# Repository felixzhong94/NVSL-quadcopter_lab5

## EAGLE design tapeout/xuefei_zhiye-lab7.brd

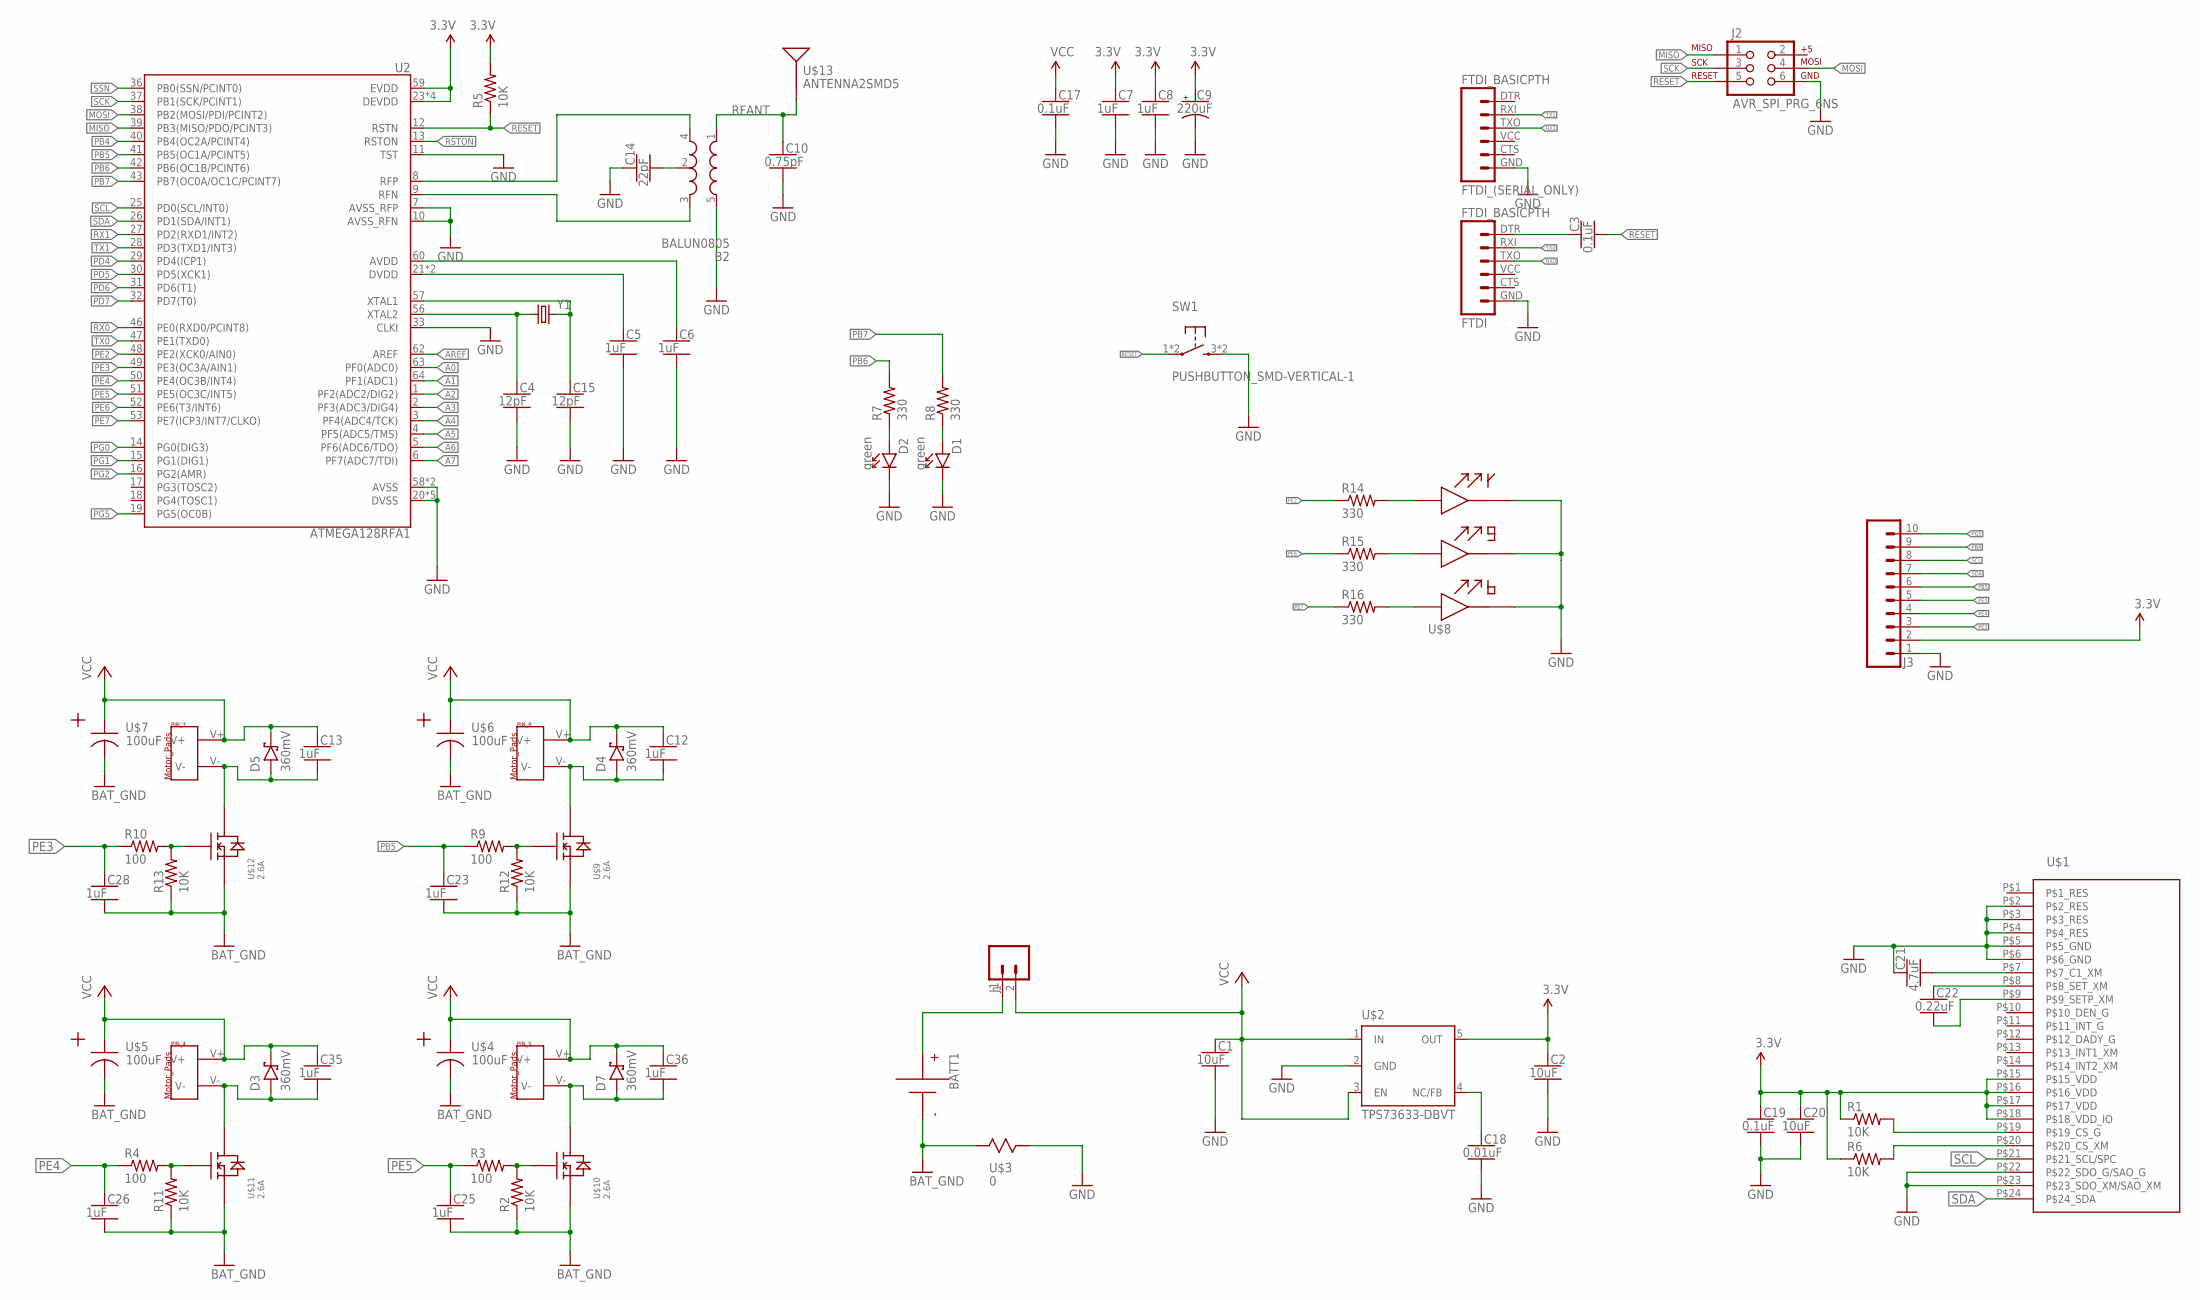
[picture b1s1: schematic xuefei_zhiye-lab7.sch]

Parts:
B2: BALUN0805; BALUN
BATT1: BATTERY-HUBSAN-W/HOLDER; BATTERY-W/HOLDER-380MAH-HUBSAN
C1, C2, C20: 10uF; CAPC2012X140_HS
C3, C17, C19: 0.1uF; CAPC2012X140_HS
C4, C15: 12pF; CAPC2012X140_HS
C5, C6, C7, C8, C12, C13, C23, C25, C26, C28, C35, C36: 1uF; CAPC2012X140_HS
C9: 220uF; CAPMP7343X310_HS
C10: 0.75pF; CAPC2012X140_HS
C14: 22pF; CAPC2012X140_HS
C18: 0.01uF; CAPC2012X140_HS
C21: 4.7uF; CAPC2012X140_HS
C22: 0.22uF; CAPC2012X140_HS
D1, D2: green; LEDSC125X200X120-2_HS
D3, D4, D5, D7: 360mV; SOD3716X135_HS
FTDI: FTDI_BASICPTH; FTDI_BASIC
FTDI_(SERIAL_ONLY): FTDI_BASICPTH; FTDI_BASIC
J1: MALE_HEADER_2POS-2X1-0.1IN; MALE_HEADER_2X1_0.1IN
J2: AVR_SPI_PRG_6NS; 2X3-NS
J3: SIP-10_TH-254X10-1; HDRV10W63P254_10X1_2540X254H838_HS
PIN_3, PIN_4, PIN_5, PIN_8: MOTOR_PADS
R1, R2, R5, R6, R11, R12, R13: 10K; RESC2012X60_HS
R3, R4, R9, R10: 100; RESC2012X60_HS
R7, R8, R14, R15, R16: 330; RESC2012X60_HS
SW1: PUSHBUTTON_SMD-VERTICAL-1; TE_FSM8JSMA_HS
U2: ATMEGA128RFA1; QFN-64
U$1: IMU; LGA-24_4X4MM
U$2: TPS73633-DBVT; SOT23-DBV
U$3: 0; SMD_RESISTOR
U$4, U$5, U$6, U$7: 100uF; TAJB_SMB_POLAR_CAP
U$8: QBLP679E-RGB
U$9, U$10, U$11, U$12: 2.6A; LITTLE_FOOT_MOSFET_W/_HEAT_SPREADER
U$13: ANTENNA2SMD5; ANTENNA-CHIP5
Y1: CRYSTAL5X3; CRYSTAL-SMD-5X3

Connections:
3.3V: C2.1, C7.1, C8.1, C9.1 (+), C19.1, C20.1, J3.2, R1.1, R5.2, R6.1, U2.23 (DEVDD), U2.34 (DEVDD), U2.44 (DEVDD), U2.54 (DEVDD), U2.59 (EVDD), U$1.P$15 (P$15_VDD), U$1.P$16 (P$16_VDD), U$1.P$17 (P$17_VDD), U$1.P$18 (P$18_VDD_IO), U$2.5 (OUT)
A0: U2.63 (PF0(ADC0))
A1: U2.64 (PF1(ADC1))
A2: U2.1 (PF2(ADC2/DIG2))
A3: U2.2 (PF3(ADC3/DIG4))
A4: U2.3 (PF4(ADC4/TCK))
A5: U2.4 (PF5(ADC5/TMS))
A6: U2.5 (PF6(ADC6/TDO))
A7: U2.6 (PF7(ADC7/TDI))
AREF: U2.62 (AREF)
AVDD: C6.1, U2.60 (AVDD)
BAT_GND: BATT1.- (N), C23.2, C25.2, C26.2, C28.2, R2.1, R11.1, R12.1, R13.1, U$3.P$1, U$4.P$2 (2), U$5.P$2 (2), U$6.P$2 (2), U$7.P$2 (2), U$9.P$2 (P$2_S), U$10.P$2 (P$2_S), U$11.P$2 (P$2_S), U$12.P$2 (P$2_S)
DTR: C3.1, FTDI.DTR (1)
DVDD: C5.1, U2.21 (DVDD), U2.22 (DVDD)
GND: B2.5 (GND), C1.2, C2.2, C4.2, C5.2, C6.2, C7.2, C8.2, C9.2 (-), C10.2, C14.1, C15.2, C17.2, C18.2, C19.2, C20.2, C21.1, D1.C, D2.C, FTDI.GND (6), FTDI_(SERIAL_ONLY).GND (6), J2.6, J3.1, SW1.3 (2), SW1.4 (2), U2.7 (AVSS_RFP), U2.10 (AVSS_RFN), U2.11 (TST), U2.20 (DVSS), U2.24 (DVSS), U2.33 (CLKI), U2.35 (DVSS), U2.45 (DVSS), U2.55 (DVSS), U2.58 (AVSS), U2.61 (AVSS), U$1.P$2 (P$2_RES), U$1.P$3 (P$3_RES), U$1.P$4 (P$4_RES), U$1.P$5 (P$5_GND), U$1.P$6 (P$6_GND), U$1.P$22 (P$22_SDO_G/SAO_G), U$1.P$23 (P$23_SDO_XM/SAO_XM), U$2.2 (GND), U$3.P$2, U$8.P$1, U$8.P$2, U$8.P$3
MISO: J2.1, U2.39 (PB3(MISO/PDO/PCINT3))
MOSI: J2.4, U2.38 (PB2(MOSI/PDI/PCINT2))
unnamed: R14.2, U$8.P$4
unnamed: R15.2, U$8.P$5
unnamed: C15.1, U2.57 (XTAL1), Y1.3 (2)
unnamed: C4.1, U2.56 (XTAL2), Y1.1
unnamed: C18.1, U$2.4 (NC/FB)
unnamed: C21.2, U$1.P$7 (P$7_C1_XM)
unnamed: B2.2 (GND), C14.2
unnamed: D2.A, R7.1
unnamed: R16.2, U$8.P$6
unnamed: C22.1, U$1.P$8 (P$8_SET_XM)
unnamed: D1.A, R8.1
unnamed: C22.2, U$1.P$9 (P$9_SETP_XM)
unnamed: R1.2, U$1.P$19 (P$19_CS_G)
unnamed: R6.2, U$1.P$20 (P$20_CS_XM)
unnamed: BATT1.+, J1.1
unnamed: R9.2, R12.2, U$9.P$1 (P$1_G)
unnamed: C12.2, D4.A, PIN_8.V-, U$9.P$3 (P$3_D)
unnamed: R2.2, R3.2, U$10.P$1 (P$1_G)
unnamed: C36.2, D7.A, PIN_5.V-, U$10.P$3 (P$3_D)
unnamed: R10.2, R13.2, U$12.P$1 (P$1_G)
unnamed: C13.2, D5.A, PIN_3.V-, U$12.P$3 (P$3_D)
unnamed: R4.2, R11.2, U$11.P$1 (P$1_G)
unnamed: C35.2, D3.A, PIN_4.V-, U$11.P$3 (P$3_D)
PB4: J3.9, U2.40 (PB4(OC2A/PCINT4))
PB5: C23.1, J3.6, R9.1, U2.41 (PB5(OC1A/PCINT5))
PB6: R7.2, U2.42 (PB6(OC1B/PCINT6))
PB7: R8.2, U2.43 (PB7(OC0A/OC1C/PCINT7))
PD4: U2.29 (PD4(ICP1))
PD5: U2.30 (PD5(XCK1))
PD6: U2.31 (PD6(T1))
PD7: U2.32 (PD7(T0))
PE2: R14.1, U2.48 (PE2(XCK0/AIN0))
PE3: C28.1, J3.3, R10.1, U2.49 (PE3(OC3A/AIN1))
PE4: C26.1, J3.4, R4.1, U2.50 (PE4(OC3B/INT4))
PE5: C25.1, J3.5, R3.1, U2.51 (PE5(OC3C/INT5))
PE6: R15.1, U2.52 (PE6(T3/INT6))
PE7: R16.1, U2.53 (PE7(ICP3/INT7/CLKO))
PG0: U2.14 (PG0(DIG3))
PG1: U2.15 (PG1(DIG1))
PG2: U2.16 (PG2(AMR))
PG5: J3.10, U2.19 (PG5(OC0B))
RESET: C3.2, J2.5, R5.1, SW1.1, SW1.2 (1), U2.12 (RSTN)
RFANT: B2.1 (IN), C10.1, U$13.FEED
RFN: B2.3 (OUT2), U2.9 (RFN)
RFP: B2.4 (OUT1), U2.8 (RFP)
RSTON: U2.13 (RSTON)
RX0: FTDI.TXO (3), U2.46 (PE0(RXD0/PCINT8))
RX1: FTDI_(SERIAL_ONLY).TXO (3), U2.27 (PD2(RXD1/INT2))
SCK: J2.3, U2.37 (PB1(SCK/PCINT1))
SCL: J3.8, U2.25 (PD0(SCL/INT0)), U$1.P$21 (P$21_SCL/SPC)
SDA: J3.7, U2.26 (PD1(SDA/INT1)), U$1.P$24 (P$24_SDA)
SSN: U2.36 (PB0(SSN/PCINT0))
TX0: FTDI.RXI (2), U2.47 (PE1(TXD0))
TX1: FTDI_(SERIAL_ONLY).RXI (2), U2.28 (PD3(TXD1/INT3))
VCC: C1.1, C12.1, C13.1, C17.1, C35.1, C36.1, D3.C, D4.C, D5.C, D7.C, J1.2, PIN_3.V+, PIN_4.V+, PIN_5.V+, PIN_8.V+, U$2.1 (IN), U$2.3 (EN), U$4.P$1 (1), U$5.P$1 (1), U$6.P$1 (1), U$7.P$1 (1)

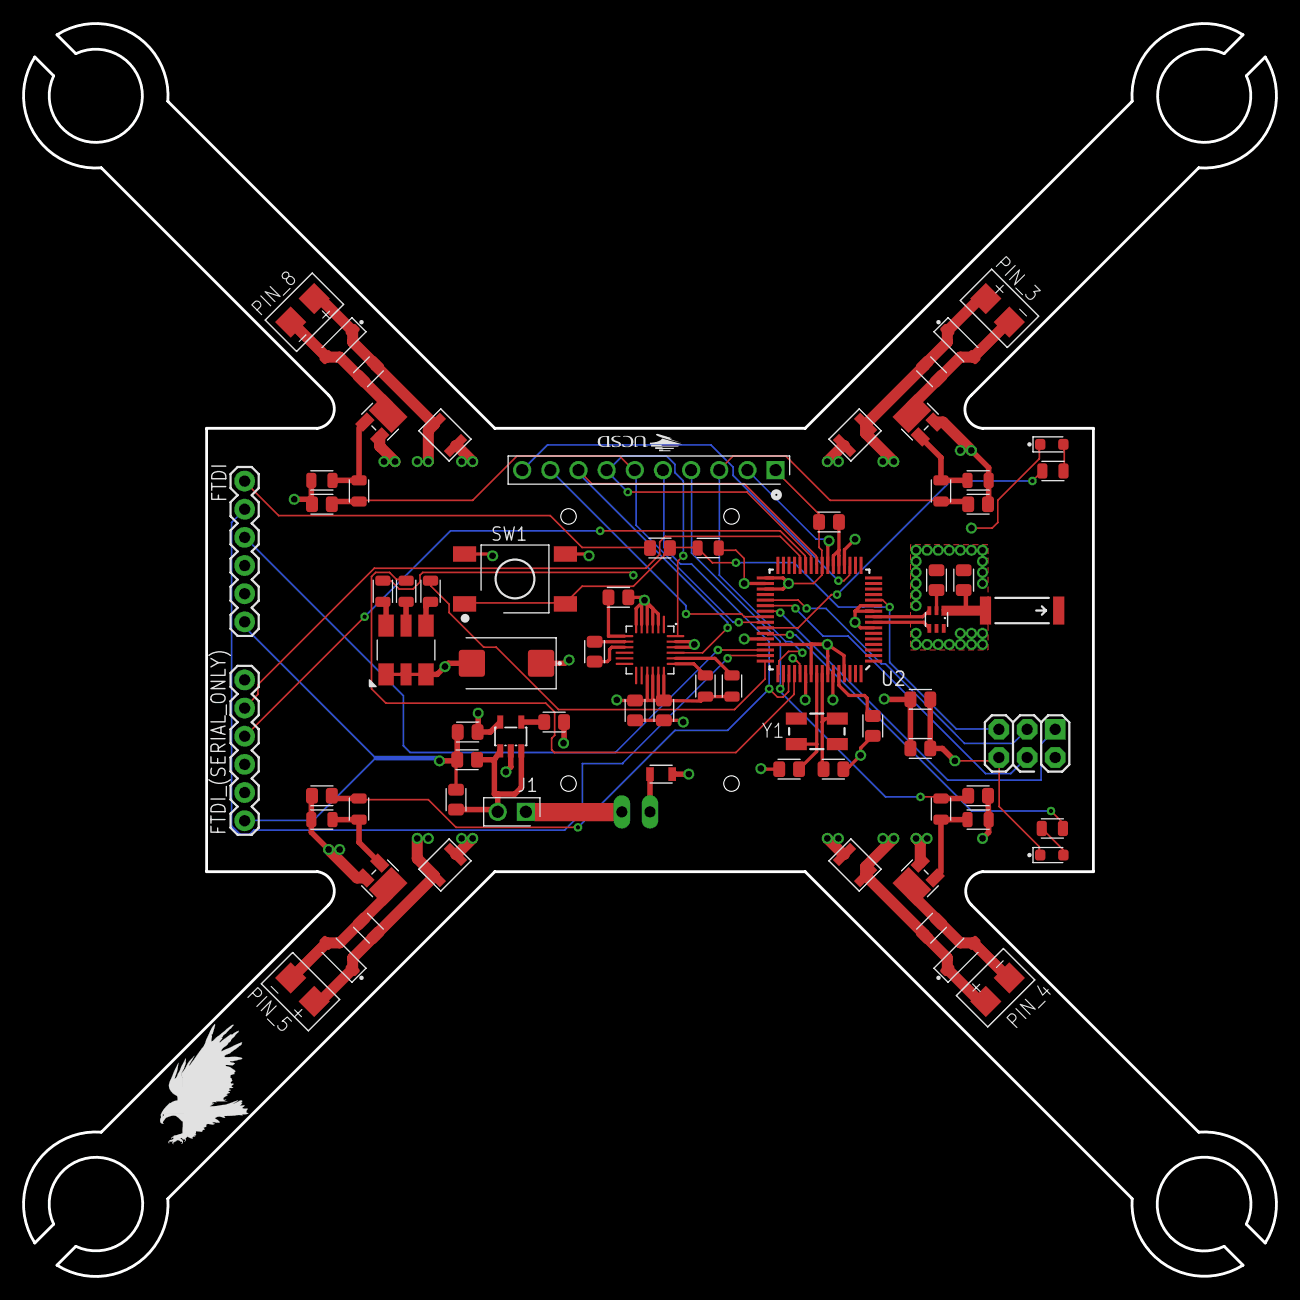
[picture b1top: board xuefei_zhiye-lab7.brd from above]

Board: 4 copper layers, 113.0 x 113.0 mm, 77 parts (1 on the bottom side), 54 nets.

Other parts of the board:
U$14: UCSD_LOGO
U$15: EAGLE-PLC-8MM

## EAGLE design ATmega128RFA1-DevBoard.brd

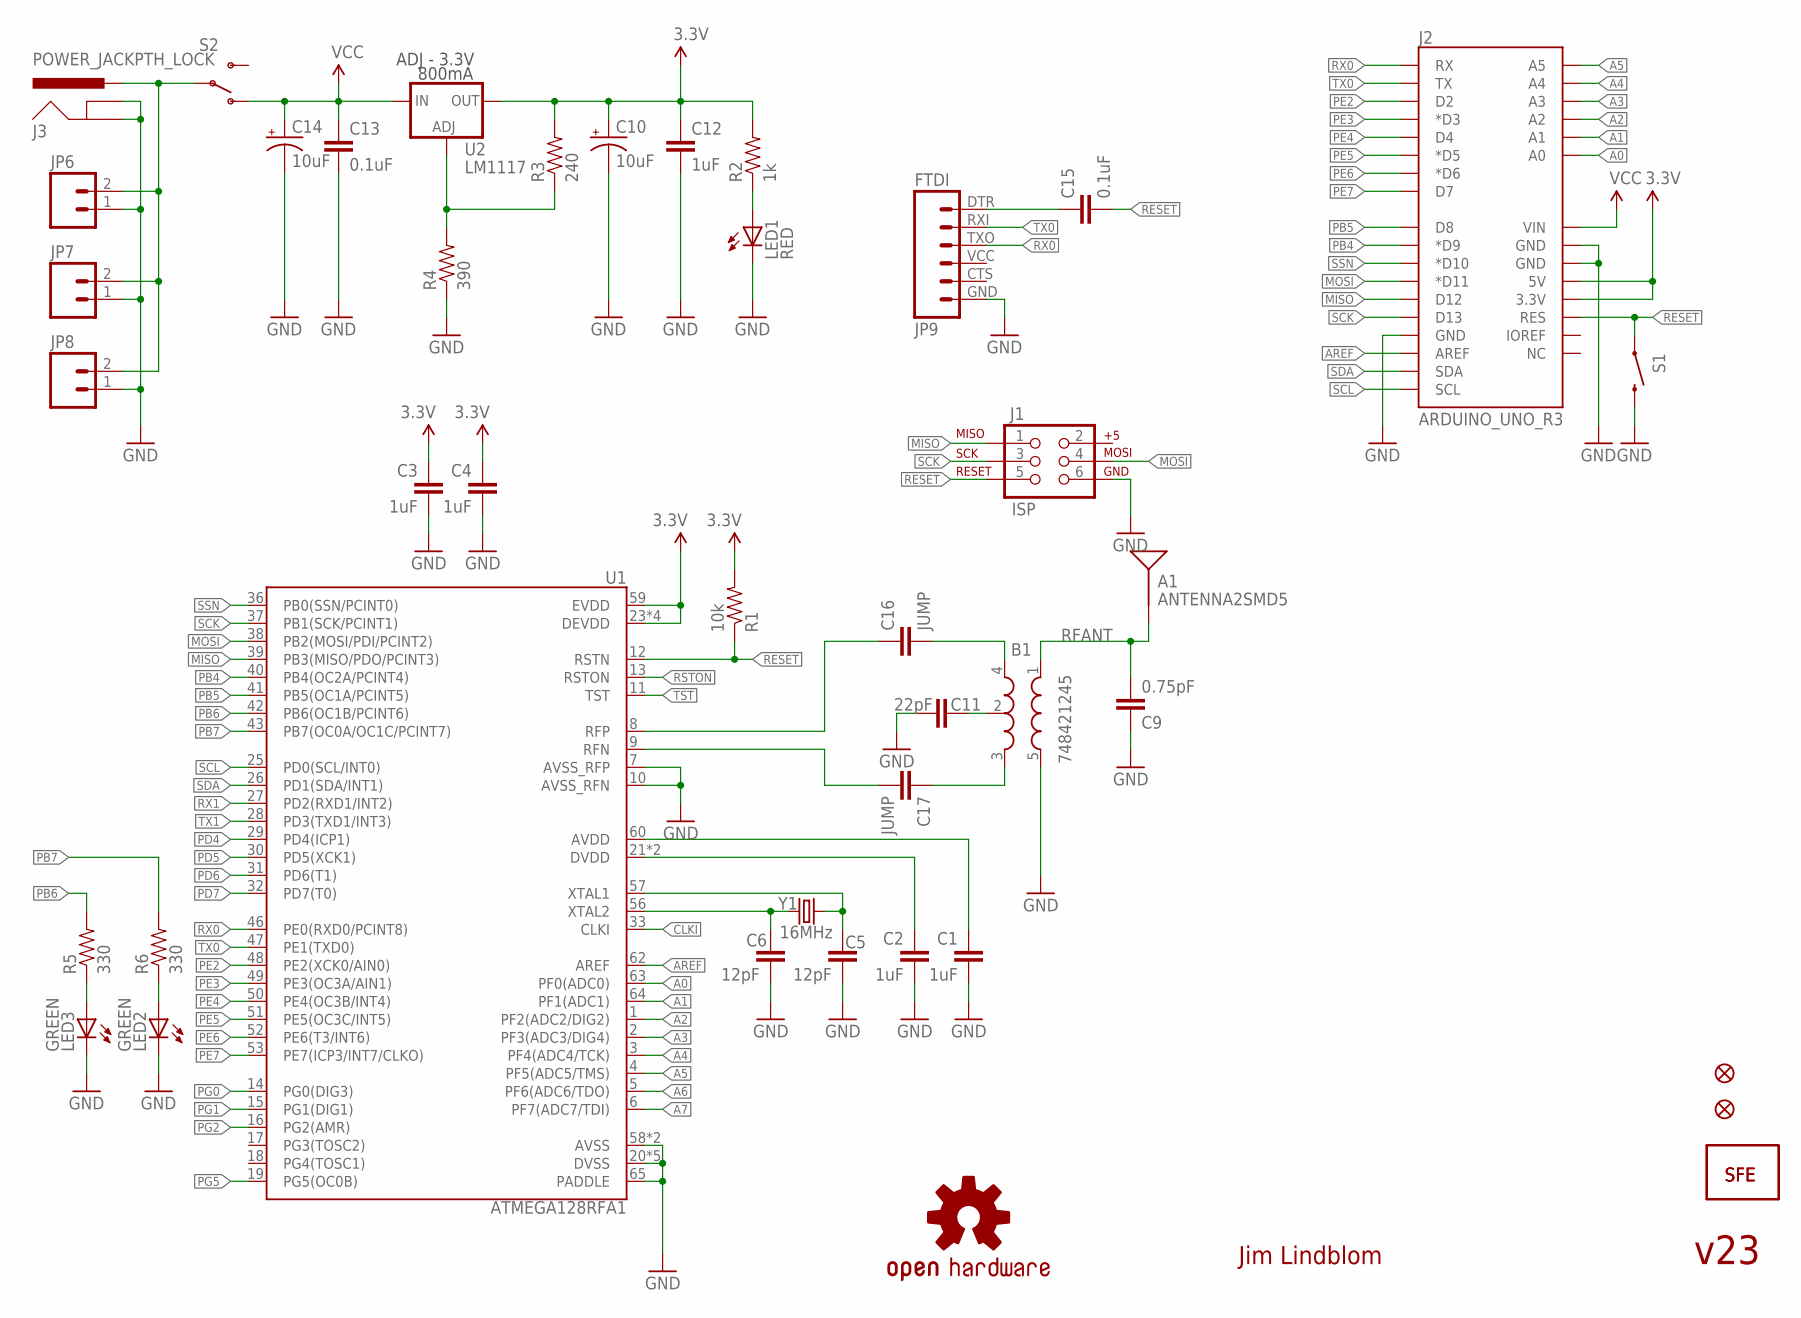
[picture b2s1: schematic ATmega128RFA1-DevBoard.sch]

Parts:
A1: ANTENNA2SMD5; ANTENNA-CHIP5
B1: 748421245; BALUN
C1, C2, C3, C4, C12: 1uF; 0402-CAP
C5, C6: 12pF; 0402-CAP
C9: 0.75pF; 0402-CAP
C10, C14: 10uF; EIA3216
C11: 22pF; 0402-CAP
C13, C15: 0.1uF; 0402-CAP
C16, C17: JUMP; 0402-CAP
FID1, FID2: FIDUCIALUFIDUCIAL; MICRO-FIDUCIAL
J1: ISP; 2X3-NS
J2: ARDUINO_UNO_R3
J3: POWER_JACKPTH_LOCK; POWER_JACK_PTH_LOCK
JP4, JP10: LOGO-SFENEW; SFE-NEW-WEBLOGO
JP6: M02JST-PTH-2; JST-2-PTH
JP7: M021X02_NO_SILK; 1X02_NO_SILK
JP8: M023.5MM-NO_SILK; SCREWTERMINAL-3.5MM-2-NS
JP9: FTDI; FTDI_BASIC
LED1: RED; LED-0603
LED2, LED3: GREEN; LED-0603
R1: 10k; 0402-RES
R2: 1k; 0402-RES
R3: 240; 0402-RES
R4: 390; 0402-RES
R5, R6: 330; 0402-RES
S1: SWITCH-MOMENTARY-2SMD; TACTILE_SWITCH_SMD
S2: SWITCH-SPST-SMD-A
U1: ATMEGA128RFA1; QFN-64
U2: LM1117; SOT223
U$1: OSHW-LOGOS; OSHW-LOGO-S
Y1: 16MHz; CRYSTAL-SMD-5X3

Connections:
3.3V: C3.1, C4.1, C10.A (+), C12.1, J2.3.3V, J2.5V, R1.2, R2.2, R3.2, U1.23 (DEVDD), U1.34 (DEVDD), U1.44 (DEVDD), U1.54 (DEVDD), U1.59 (EVDD), U2.2 (OUT)
A0: J2.A0, U1.63 (PF0(ADC0))
A1: J2.A1, U1.64 (PF1(ADC1))
A2: J2.A2, U1.1 (PF2(ADC2/DIG2))
A3: J2.A3, U1.2 (PF3(ADC3/DIG4))
A4: J2.A4, U1.3 (PF4(ADC4/TCK))
A5: J2.A5, U1.4 (PF5(ADC5/TMS))
A6: U1.5 (PF6(ADC6/TDO))
A7: U1.6 (PF7(ADC7/TDI))
AREF: J2.AREF, U1.62 (AREF)
AVDD: C1.1, U1.60 (AVDD)
CLKI: U1.33 (CLKI)
DTR: C15.1, JP9.DTR (1)
DVDD: C2.1, U1.21 (DVDD), U1.22 (DVDD)
FB: R3.1, R4.2, U2.1 (ADJ)
GND: B1.5 (GND), C1.2, C2.2, C3.2, C4.2, C5.2, C6.2, C9.1, C10.C (-), C11.2, C12.2, C13.2, C14.C (-), J1.6, J2.GND@0 (GND), J2.GND@1 (GND), J2.GND@2 (GND), J3.GND, J3.GNDBREAK, JP6.1, JP7.1, JP8.1, JP9.GND (6), LED1.C, LED2.C, LED3.C, R4.1, S1.3 (2), U1.7 (AVSS_RFP), U1.10 (AVSS_RFN), U1.20 (DVSS), U1.24 (DVSS), U1.35 (DVSS), U1.45 (DVSS), U1.55 (DVSS), U1.58 (AVSS), U1.61 (AVSS), U1.65 (PADDLE)
MISO: J1.1, J2.D12, U1.39 (PB3(MISO/PDO/PCINT3))
MOSI: J1.4, J2.D11 (*D11), U1.38 (PB2(MOSI/PDI/PCINT2))
unnamed: LED1.A, R2.1
unnamed: C5.1, U1.57 (XTAL1), Y1.3 (2)
unnamed: C6.1, U1.56 (XTAL2), Y1.1
unnamed: B1.2 (GND), C11.1
unnamed: LED3.A, R5.1
unnamed: J3.PWR, JP6.2, JP7.2, JP8.2, S2.2
unnamed: B1.4 (OUT1), C16.2
unnamed: B1.3 (OUT2), C17.1
unnamed: LED2.A, R6.1
PB4: J2.D9 (*D9), U1.40 (PB4(OC2A/PCINT4))
PB5: J2.D8, U1.41 (PB5(OC1A/PCINT5))
PB6: R5.2, U1.42 (PB6(OC1B/PCINT6))
PB7: R6.2, U1.43 (PB7(OC0A/OC1C/PCINT7))
PD4: U1.29 (PD4(ICP1))
PD5: U1.30 (PD5(XCK1))
PD6: U1.31 (PD6(T1))
PD7: U1.32 (PD7(T0))
PE2: J2.D2, U1.48 (PE2(XCK0/AIN0))
PE3: J2.D3 (*D3), U1.49 (PE3(OC3A/AIN1))
PE4: J2.D4, U1.50 (PE4(OC3B/INT4))
PE5: J2.D5 (*D5), U1.51 (PE5(OC3C/INT5))
PE6: J2.D6 (*D6), U1.52 (PE6(T3/INT6))
PE7: J2.D7, U1.53 (PE7(ICP3/INT7/CLKO))
PG0: U1.14 (PG0(DIG3))
PG1: U1.15 (PG1(DIG1))
PG2: U1.16 (PG2(AMR))
PG5: U1.19 (PG5(OC0B))
RESET: C15.2, J1.5, J2.RES, R1.1, S1.1, U1.12 (RSTN)
RFANT: A1.FEED, B1.1 (IN), C9.2
RFN: C17.2, U1.9 (RFN)
RFP: C16.1, U1.8 (RFP)
RSTON: U1.13 (RSTON)
RX0: J2.RX, JP9.TXO (3), U1.46 (PE0(RXD0/PCINT8))
RX1: U1.27 (PD2(RXD1/INT2))
S$2: J1.2
SCK: J1.3, J2.D13, U1.37 (PB1(SCK/PCINT1))
SCL: J2.SCL, U1.25 (PD0(SCL/INT0))
SDA: J2.SDA, U1.26 (PD1(SDA/INT1))
SSN: J2.D10 (*D10), U1.36 (PB0(SSN/PCINT0))
TST: U1.11 (TST)
TX0: J2.TX, JP9.RXI (2), U1.47 (PE1(TXD0))
TX1: U1.28 (PD3(TXD1/INT3))
VCC: C13.1, C14.A (+), J2.VIN, S2.1 (O), U2.3 (IN)

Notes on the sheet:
Jim Lindblom
800mA
ADJ - 3.3V
v23

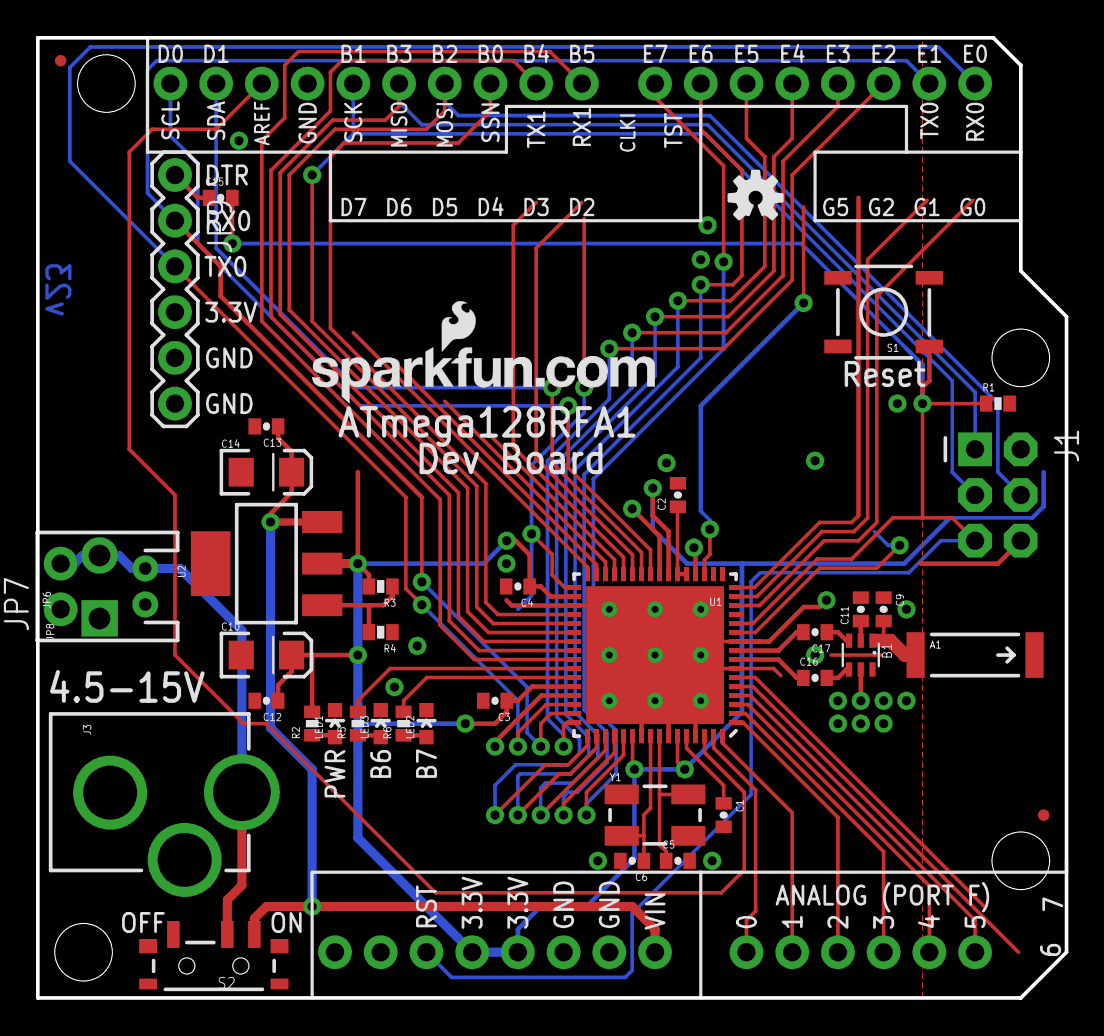
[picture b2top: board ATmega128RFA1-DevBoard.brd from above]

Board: 2 copper layers, 57.1 x 53.3 mm, 43 parts (1 on the bottom side), 45 nets.

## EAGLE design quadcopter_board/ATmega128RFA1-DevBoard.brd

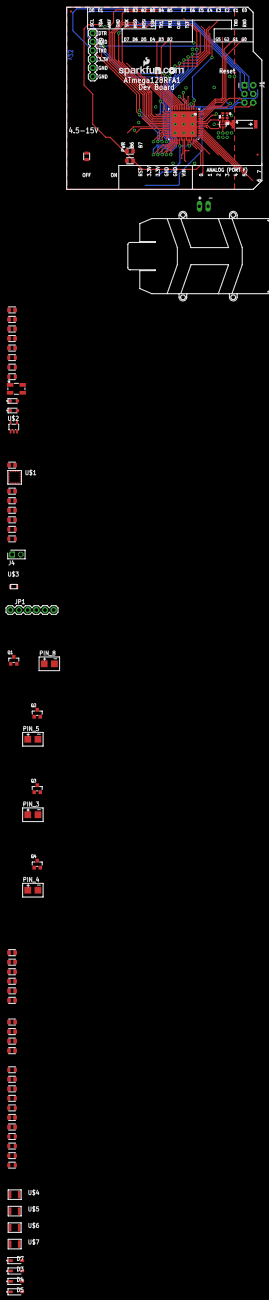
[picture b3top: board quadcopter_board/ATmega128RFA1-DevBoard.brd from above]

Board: 2 copper layers, 57.1 x 53.3 mm, 75 parts (1 on the bottom side), 46 nets.

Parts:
A1: ANTENNA2SMD5; ANTENNA-CHIP5
B1: 748421245; BALUN
BATT1: BATTERY-HUBSAN-W/HOLDER; BATTERY-W/HOLDER-380MAH-HUBSAN
C1, C2, C20: 10uF; CAPC2012X140_HS
C3, C17, C19: 0.1uF; CAPC2012X140_HS
C4, C15: 12pF; CAPC2012X140_HS
C5, C6, C7, C8, C12, C13, C16, C23, C25, C26, C28, C35, C36: 1uF; CAPC2012X140_HS
C9: 0.75pF; 0402-CAP
C10: 0.75pF; CAPC2012X140_HS
C11: 22pF; 0402-CAP
C14: 22pF; CAPC2012X140_HS
C18: 0.01uF; CAPC2012X140_HS
C21: 4.7uF; CAPC2012X140_HS
C22: 0.22uF; CAPC2012X140_HS
D1, D2: green; LEDSC125X200X120-2_HS
D3, D4, D5, D7: 360mV; SOD3716X135_HS
FID1, FID2: FIDUCIALUFIDUCIAL; MICRO-FIDUCIAL
J1: ISP; 2X3-NS
J4: MALE_HEADER_2X1_0.1IN
JP1: FTDI (Serial Only); FTDI_BASIC
JP4, JP10: LOGO-SFENEW; SFE-NEW-WEBLOGO
JP9: FTDI; FTDI_BASIC
PIN_3, PIN_4, PIN_5, PIN_8: MOTOR_PADS
Q1, Q2, Q3, Q4: CJ2302; SOT-23
R1, R2, R5, R6, R11, R12, R13: 10K; RESC2012X60_HS
R3, R4, R9, R10: 100; RESC2012X60_HS
R7, R8: 330; RESC2012X60_HS
U1: ATMEGA128RFA1; QFN-64
U$1: IMU; LGA-24_4X4MM
U$2: TPS73633-DBVT; SOT23-DBV
U$3: 0; SMD_RESISTOR
U$4, U$5, U$6, U$7: 100uF; TAJB_SMB_POLAR_CAP
Y2: CRYSTAL-SMD-5X3

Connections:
3.3V: C2.1, C7.1, C8.1, C16.1, C19.1, C20.1, R1.1, R5.2, R6.1, U1.23, U1.34, U1.44, U1.54, U1.59, U$1.P$15, U$1.P$16, U$1.P$17, U$1.P$18, U$2.5
AVDD: C6.1, U1.60
BAT_GND: BATT1.-, C23.2, C25.2, C26.2, C28.2, Q1.2, Q2.2, Q3.2, Q4.2, R2.1, R11.1, R12.1, R13.1, U$3.P$1, U$4.P$2, U$5.P$2, U$6.P$2, U$7.P$2
DTR: C3.1, JP9.DTR
DVDD: C5.1, U1.21, U1.22
GND: B1.5, C1.2, C2.2, C4.2, C5.2, C6.2, C7.2, C8.2, C9.1, C11.2, C15.2, C16.2, C17.2, C18.2, C19.2, C20.2, C21.1, D1.C, D2.C, J1.6, JP1.GND, JP9.GND, U1.7, U1.10, U1.11, U1.20, U1.24, U1.33, U1.35, U1.45, U1.55, U1.58, U1.61, U1.65, U$1.P$2, U$1.P$3, U$1.P$4, U$1.P$5, U$1.P$6, U$1.P$22, U$1.P$23, U$2.2, U$3.P$2
MISO: J1.1, U1.39
MOSI: J1.4, U1.38
unnamed: C15.1, U1.57, Y2.3
unnamed: C4.1, U1.56, Y2.1
unnamed: C18.1, U$2.4
unnamed: C21.2, U$1.P$7
unnamed: B1.2, C11.1
unnamed: D2.A, R7.1
unnamed: C22.1, U$1.P$8
unnamed: D1.A, R8.1
unnamed: C22.2, U$1.P$9
unnamed: R1.2, U$1.P$19
unnamed: R6.2, U$1.P$20
unnamed: BATT1.+, J4.1
unnamed: Q1.1, R9.2, R12.2
unnamed: C12.2, D4.A, PIN_8.V-, Q1.3
unnamed: Q2.1, R2.2, R3.2
unnamed: C36.2, D7.A, PIN_5.V-, Q2.3
unnamed: Q3.1, R10.2, R13.2
unnamed: C13.2, D5.A, PIN_3.V-, Q3.3
unnamed: Q4.1, R4.2, R11.2
unnamed: C35.2, D3.A, PIN_4.V-, Q4.3
PB5: C23.1, R9.1, U1.41
PB6: R7.2, U1.42
PB7: R8.2, U1.43
PE3: C28.1, R10.1, U1.49
PE4: C26.1, R4.1, U1.50
PE5: C25.1, R3.1, U1.51
RESET: C3.2, J1.5, R5.1, U1.12
RFANT: A1.FEED, B1.1, C9.2
RFN: B1.3, U1.9
RFP: B1.4, U1.8
RX0: JP9.TXO, U1.46
RX1: JP1.RXI, U1.27
SCK: J1.3, U1.37
SCL: U1.25, U$1.P$21
SDA: U1.26, U$1.P$24
TX0: JP9.RXI, U1.47
TX1: JP1.TXO, U1.28
VCC: C1.1, C12.1, C13.1, C17.1, C35.1, C36.1, D3.C, D4.C, D5.C, D7.C, J4.2, PIN_3.V+, PIN_4.V+, PIN_5.V+, PIN_8.V+, U$2.1, U$2.3, U$4.P$1, U$5.P$1, U$6.P$1, U$7.P$1

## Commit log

2016-04-20 added base
2016-04-21 added and wired imu
2016-04-21 added motor controller
2016-04-21 added bigger cap to power supply
2016-04-21 added tags
2016-04-22 clear up of motor driver layout
2016-04-26 changed component on motor driver
2016-04-26 devboard changes
2016-04-29 Reviewed on board schematic and documentations
2016-04-30 finished general review first pass
2016-04-30 I did NOT write this; my name shouldn't be on it.
2016-04-30 Wrote this a few days ago but wasn't aware I was supposed to commit it
2016-05-02 added rgb led and removed unneeded files
2016-05-03 Made corrections
2016-05-05 parts placed
2016-05-05 POURED SHIELDING FOR ANT
2016-05-05 FIXED SOME POURS
2016-05-07 For Design Review
2016-05-08 fixed/corrected library fields
2016-05-08 Updated board with new prebuilt library and resolved keep-out conflicts
2016-05-12 Applied update to library and dru files. Passing DFM testing
2016-05-13 Commit the list of questions you had about the reviewee's design
2016-05-17 fixed
2016-05-17 fixed outline
2016-05-17 fixed imu smd width
2016-05-17 Tape-Out

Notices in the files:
parts and their libraries:
SparkFun-DigitalIC: Licensing: CC v3.0 Share-Alike You are welcome to use this library for commercial purposes.
SparkFun-Aesthetics: Released under the Creative Commons
SparkFun-Aesthetics: http://creativecommons.org/licenses/by-sa/3.0
